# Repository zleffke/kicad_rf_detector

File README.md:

# kicad_rf_detector
RF Detector Circuit

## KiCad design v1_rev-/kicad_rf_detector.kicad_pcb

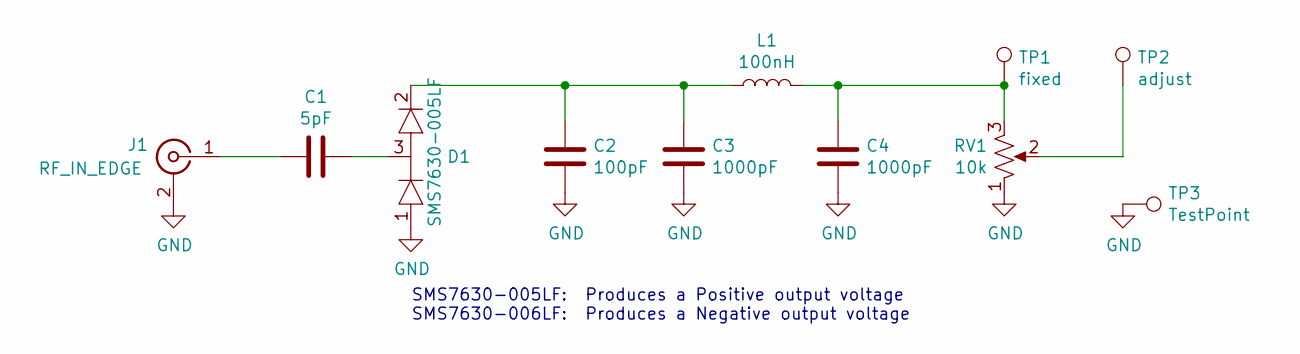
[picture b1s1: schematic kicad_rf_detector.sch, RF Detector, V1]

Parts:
C1: 5pF; 0805
C2: 100pF; 0805
C3, C4: 1000pF; 0805
D1: SMS7630-005LF; SOT-23-3
J1: RF_IN_EDGE; SMA_Samtec_SMA-J-P-X-ST-EM1_EdgeMount
L1: 100nH; L_0805_2012Metric
RV1: 10k; Potentiometer_Bourns_3314G_Vertical
TP1: fixed; TestPoint_Pad_2.0x2.0mm
TP2: adjust; TestPoint_Pad_2.0x2.0mm
TP3: TestPoint; TestPoint_Pad_2.0x2.0mm

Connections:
GND: C2.1, C3.1, C4.1, D1.1, J1.2 (Ext), RV1.1, TP3.1
unnamed: C1.1, D1.3
unnamed: C1.2, J1.1 (In)
unnamed: C2.2, C3.2, D1.2, L1.1
unnamed: C4.2, L1.2, RV1.3, TP1.1
unnamed: RV1.2, TP2.1

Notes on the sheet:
SMS7630-005LF: Produces a Positive output voltage SMS7630-006LF: Produces a Negative output voltage

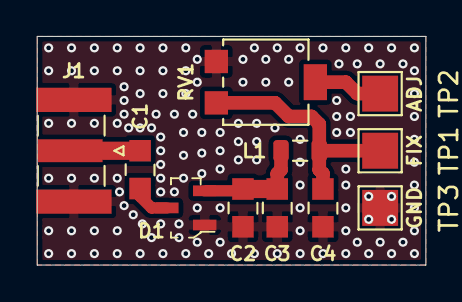
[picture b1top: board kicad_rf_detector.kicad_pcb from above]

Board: 2 copper layers, 21.6 x 12.7 mm, 11 parts (0 on the bottom side), 6 nets.

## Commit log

2021-06-02 this version submitted to Osh Park, completed version.

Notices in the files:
v1_rev-/kicad_rf_detector.kicad_pcb:
License: CC BY 4.0
v1_rev-/kicad_rf_detector.sch:
creativecommons.org/licenses/by/4.0
